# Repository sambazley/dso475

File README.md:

# USB Interface for Gould 475 Oscilloscope

PCB and software to interface a Gould 475 oscilloscope with a PC over USB.

The STM32 software interprets the HPGL that is output from the oscilloscope and
converts it to SVG format. The SVG data is transmitted to dsoctl over USB.

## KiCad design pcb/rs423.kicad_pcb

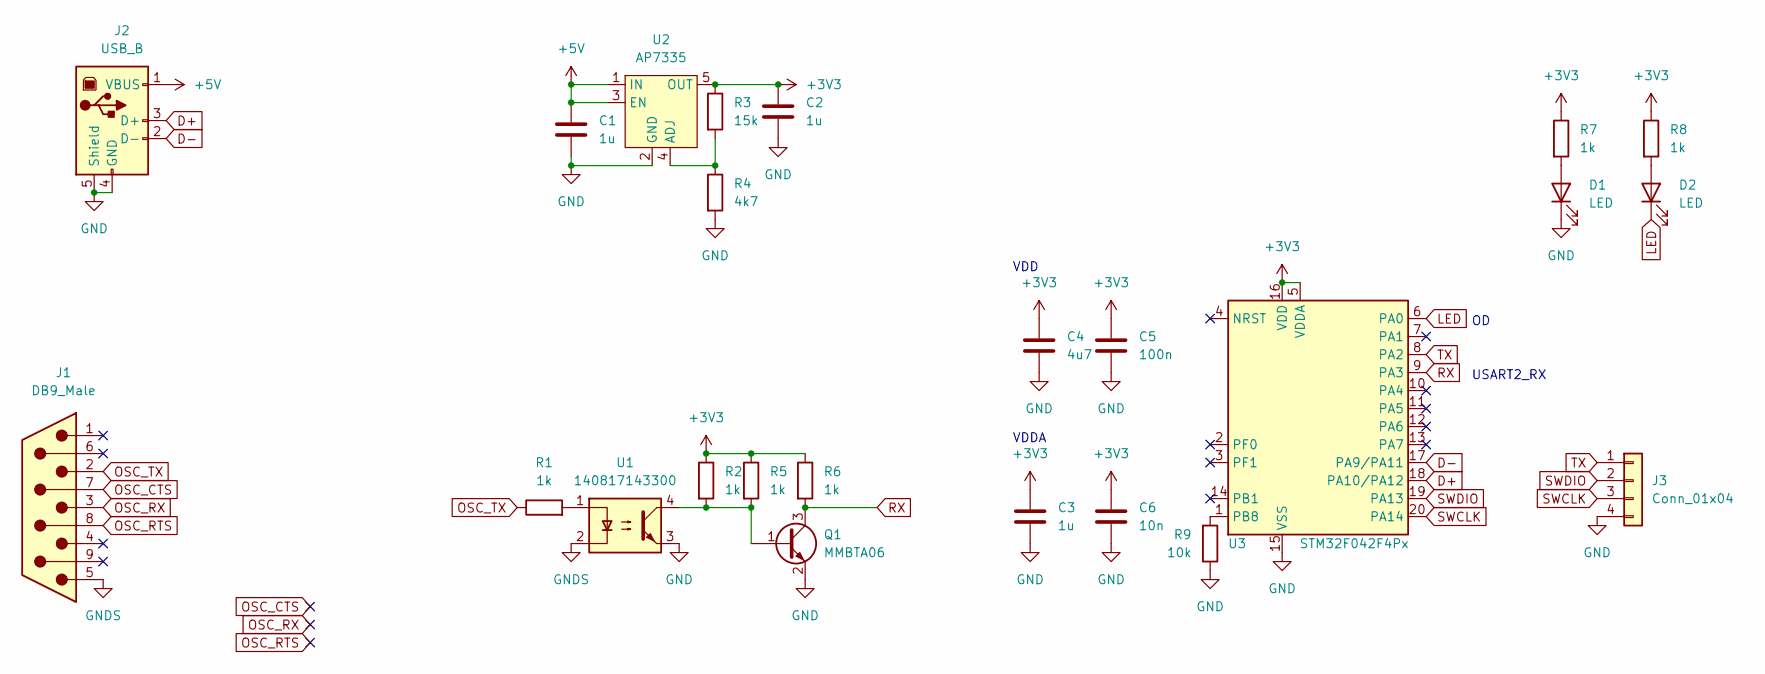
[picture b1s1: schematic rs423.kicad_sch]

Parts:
C1, C2, C3: 1u; C_0805_2012Metric
C4: 4u7; C_0805_2012Metric
C5: 100n; C_0805_2012Metric
C6: 10n; C_0805_2012Metric
D1, D2: LED; LED_0805_2012Metric
J1: DB9_Male; A-DS 09 A_KG-T4S
J2: USB_B; UJ2-BH-TH
J3: Conn_01x04; PinHeader_1x04_P2.54mm_Vertical
Q1: MMBTA06; SOT-23
R1, R2, R5, R6, R7, R8: 1k; R_0805_2012Metric
R3: 15k; R_0805_2012Metric
R4: 4k7; R_0805_2012Metric
R9: 10k; R_0805_2012Metric
U1: 140817143300; SMDIP-4_W9.53mm
U2: AP7335; SOT-23-5
U3: STM32F042F4Px; TSSOP-20_4.4x6.5mm_P0.65mm

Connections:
+3V3: C2.1, C3.1, C4.1, C5.1, C6.1, R2.1, R3.1, R5.1, R6.1, R7.1, R8.1, U2.5 (OUT), U3.5 (VDDA), U3.16 (VDD)
+5V: C1.1, J2.1 (VBUS), U2.1 (IN), U2.3 (EN)
D+: J2.3 (D+), U3.18 (PA10/PA12)
D-: J2.2 (D-), U3.17 (PA9/PA11)
GND: C1.2, C2.2, C3.2, C4.2, C5.2, C6.2, D1.1 (K), J2.4 (GND), J2.5 (Shield), J3.4, Q1.2 (E), R4.2, R9.1, U1.3, U2.2 (GND), U3.15 (VSS)
GNDS: J1.5, U1.2
LED: D2.1 (K), U3.6 (PA0)
unnamed: D1.2 (A), R7.2
unnamed: D2.2 (A), R8.2
unnamed: Q1.1 (B), R2.2, R5.2, U1.4
unnamed: R1.2, U1.1
unnamed: R3.2, R4.1, U2.4 (ADJ)
unnamed: R9.2, U3.1 (PB8)
OSC_CTS: J1.7
OSC_RTS: J1.8
OSC_RX: J1.3
OSC_TX: J1.2, R1.1
RX: Q1.3 (C), R6.2, U3.9 (PA3)
SWCLK: J3.3, U3.20 (PA14)
SWDIO: J3.2, U3.19 (PA13)
TX: J3.1, U3.8 (PA2)

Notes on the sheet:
VDD
VDDA
USART2_RX

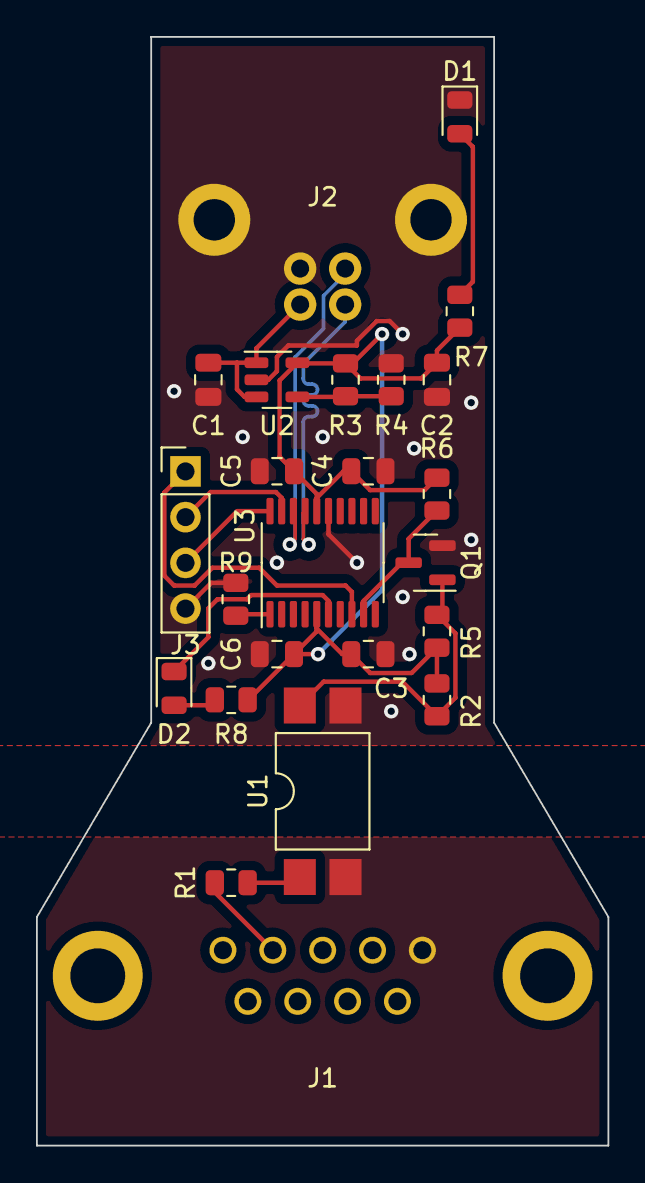
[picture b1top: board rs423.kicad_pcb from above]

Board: 2 copper layers, 31.8 x 61.6 mm, 24 parts (0 on the bottom side), 18 nets.

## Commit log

2021-10-12 Add PCB files
2021-10-12 Add STM32 code
2021-10-12 Add dsoctl
2021-10-12 Add readme and license
2021-10-16 Implement HPGL PA command for XY plots
